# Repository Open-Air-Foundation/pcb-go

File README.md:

# AirGradient GO — Hardware

> KiCad hardware design files for the AirGradient GO, a portable battery-powered air quality monitor.

<!--  -->

**This checkout is v2:** main board PCB revision 2.1, the boards in the GO v2 production units (tag `v2`, branch `main`).

## Overview

AirGradient GO is a handheld air quality monitor. It measures:
- particulate matter (Sensirion SPS30);
- CO₂ (Senseair S12);
- VOC/NOx (Sensirion SGP41);
- temperature and humidity (Sensirion SHT40);
- barometric pressure (Goermicro SPL07-003).

It also has an accelerometer (LIS2DH12) for motion detection and a GNSS receiver (TAU1113, GPS L1 and BeiDou B1) for location.

Readings are shown on a 2.13″ black-and-white e-paper display, with four RGB LEDs and capacitive touch controls. The device runs on a replaceable 18500 Li-ion cell (2600 mAh), charged over USB-C.

This repository contains the complete electronics design: schematics, PCB layouts, shared component libraries, and production outputs.

## Versions

| Version | Where | Main board revision | State |
|---|---|---|---|
| v1 | tag `v1.0` | 1.0 | the first product: pouch cell, separate LED + touch board |
| v2 | tag `v2`, branch `main` | 2.1 | **the produced boards** (this checkout) |
| v3 | branch `v3-reroute` | 3.0 | prototype |

[VERSIONS.md](https://github.com/Open-Air-Foundation/pcb-go/blob/v3-reroute/VERSIONS.md) (on branch `v3-reroute`) compares the three side by side, with pin maps and the reasons for each change.

Each version has a hardware spec sheet. It includes the parts the KiCad BOM does not define: the display, the battery and the internal cables.
- v2: [SPEC-SHEET.md](SPEC-SHEET.md)
- v1: [SPEC-SHEET-v1.md](SPEC-SHEET-v1.md)
- v3: [SPEC-SHEET.md on branch `v3-reroute`](https://github.com/Open-Air-Foundation/pcb-go/blob/v3-reroute/SPEC-SHEET.md)

The manufacturers' documents (PDF) are in [`documents/`](documents/README.md): datasheets of the main parts (ESP32-C5 module, charger, fuel gauge, power parts, sensors, peripherals), and the documents a search does not find (display, battery, Senseair S12, GNSS antenna).

[`CLAUDE.md`](CLAUDE.md) and [`AGENTS.md`](AGENTS.md) are instructions for an AI working in this repository: which git ref is which version, which document answers which question, the traps.

## Boards in this repository

| Board | Directory | Production set | Layers | Used by | Description |
|---|---|---|---|---|---|
| Main board | `PCB/airgradient-go-main/` | `Airgradient-GO_2.1` | 4 | v2 | MCU, power and charging, cell protection and fuel gauge, sensors, LEDs, storage. `Airgradient-GO_2.0` is the prototype revision |
| Touch pad | `PCB/touch-pad/` | `Touch_sensor_v2.1` | 2 | v2 | Three capacitive pads with the CAP1203 controller; 5-pin cable to the main board |
| LED + touch controller | `PCB/led-touch/` | `AG-GO-LED_1.0` | 2 | v1 only | RGB LEDs, LED driver and touch controller of v1 |
| SCD4x module | `PCB/scd4x-module/` | `SCD4x_module_0.1` | 2 | optional | CO₂ daughterboard. The standard configuration uses the on-board Senseair S12 |

## Key components (main board 2.1)

| Function | Part | Ref |
|---|---|---|
| MCU / Wi-Fi 6 + Bluetooth LE | ESP32-C5-MINI-1 (N4) | U4 |
| Battery charger | BQ25628 | U5 |
| Fuel gauge and cell protection | BQ27742-G1, with the CSD83325L FET pair | U3, Q3 |
| Input power switch | LM66200 ideal-diode switch | U19 |
| Buck-boost converter (3.1 V rail) | TPS63802 | U8 |
| LDO, GNSS backup supply | TPS7A0228 | U9 |
| Hardware watchdog | TPL5010 | U7 |
| NAND flash (512 Mb) | W25N512GVEIG | U1 |
| NAND flash, alternative footprint (not fitted) | ZDSD512MLGEAG | U2 |
| microSD socket (not fitted) | TF-CARD XG8P | TF1 |
| CO₂ sensor module | Senseair S12 | U16 |
| VOC/NOx sensor | SGP41 | U10 |
| Temperature/humidity sensor | SHT40 | U12 |
| Pressure sensor | SPL07-003 | U13 |
| Accelerometer | LIS2DH12 | U14 |
| GNSS receiver | TAU1113 | U18 |
| GNSS antenna | CA-G01 chip antenna | AE1 |
| I²C switch for the SPS30 | TMUX121 | U15 |
| I/O expander | TCA6408A | U17 |
| LED driver, 4 RGB LEDs | LP5036 | U20, LED1–LED4 |
| Buzzer | HYG-8503A | U6 |
| USB-C connector | GT-USB-7010ASV | USB1 |
| CO sensor place (not fitted) | — | U11 |

The cable connectors are HCZZ0032-5 (5-pin, 1.0 mm), referenced `CN1` to `CN3`:
- `CN1` takes the Sensirion SPS30 PM module.
- `CN2` takes the touch pad.
- `CN3` is a spare I²C header.

The cell sits in a moulded holder whose contacts are on the board (`BT1`), in a cut-out at the top of the board.

## Toolchain

- **KiCad 10** (file format 2026-03). All symbol, footprint, and 3D model libraries are bundled in `libraries/`. Each board's `fp-lib-table` / `sym-lib-table` references them project-relative, so the projects open without any extra library setup.
- **[Fabrication Toolkit](https://github.com/bennymeg/Fabrication-Toolkit)** plugin generates the Gerber/BOM/CPL production sets (`fabrication-toolkit-options.json` per board).

## Repository structure

```
PCB/
├── airgradient-go-main/     # Main PCB (schematic, layout, BOM.csv, production/)
├── touch-pad/               # Capacitive touch PCB
├── led-touch/               # LED + touch-controller PCB (v1 only)
└── scd4x-module/            # Optional SCD4x CO₂ daughterboard
libraries/                   # Shared KiCad symbols, footprints, 3D models
graphics/                    # Logos and artwork
SPEC-SHEET.md                # Hardware spec sheet of v2
SPEC-SHEET-v1.md             # Hardware spec sheet of v1
documents/                   # Manufacturers' documents: datasheets of the main parts, display, battery, S12
CLAUDE.md                    # Instructions for AI agents
AGENTS.md                    # Points other AI agents to CLAUDE.md
```

## Fabrication

Each board's `production/` directory holds a ready-to-order set: Gerber zip, BOM, designators, and pick-and-place positions in JLCPCB-compatible format (generated with Fabrication Toolkit). For v2 the sets are `Airgradient-GO_2.1` (main board) and `Touch_sensor_v2.1` (touch pad).

The main board is 4 layers, 0.8 mm thick. The touch, LED and SCD4x boards are 2 layers.

## BOM & sourcing

The schematic BOM is `PCB/airgradient-go-main/BOM.csv`. The assembly BOMs (`production/*_bom.csv`) carry LCSC part numbers for assembly at JLCPCB.

These main-board parts have no LCSC number and are supplied separately for assembly:
- ESP32-C5-MINI-1 module
- Senseair S12
- SGP41
- SHT40
- TAU1113
- CA-G01 antenna

The display, the battery and the two internal cables are not in the KiCad BOM: see [SPEC-SHEET.md](SPEC-SHEET.md). The datasheets of the main parts, and the manufacturers' documents for the display, the battery, the S12 and the GNSS antenna, are in [`documents/`](documents/README.md).

## Versioning & releases

Hardware versions are tagged on this repository: `v1.0`, `v2`. Per-version release notes, with chip-level changes, design history and the matching production file set, are published on the [GitHub Releases](../../releases) page.

## Related repositories

<!-- TODO: add links to the firmware and enclosure repositories -->

## License

This is open-source hardware. The design files in this repository are licensed under the
[Creative Commons Attribution-ShareAlike 4.0 International (CC BY-SA 4.0)](https://creativecommons.org/licenses/by-sa/4.0/) license — see [LICENSE](LICENSE).

You are free to use, modify, and manufacture these designs, including commercially, provided you credit AirGradient and share derivative designs under the same license.

## Maintainers

AirGradient hardware team.

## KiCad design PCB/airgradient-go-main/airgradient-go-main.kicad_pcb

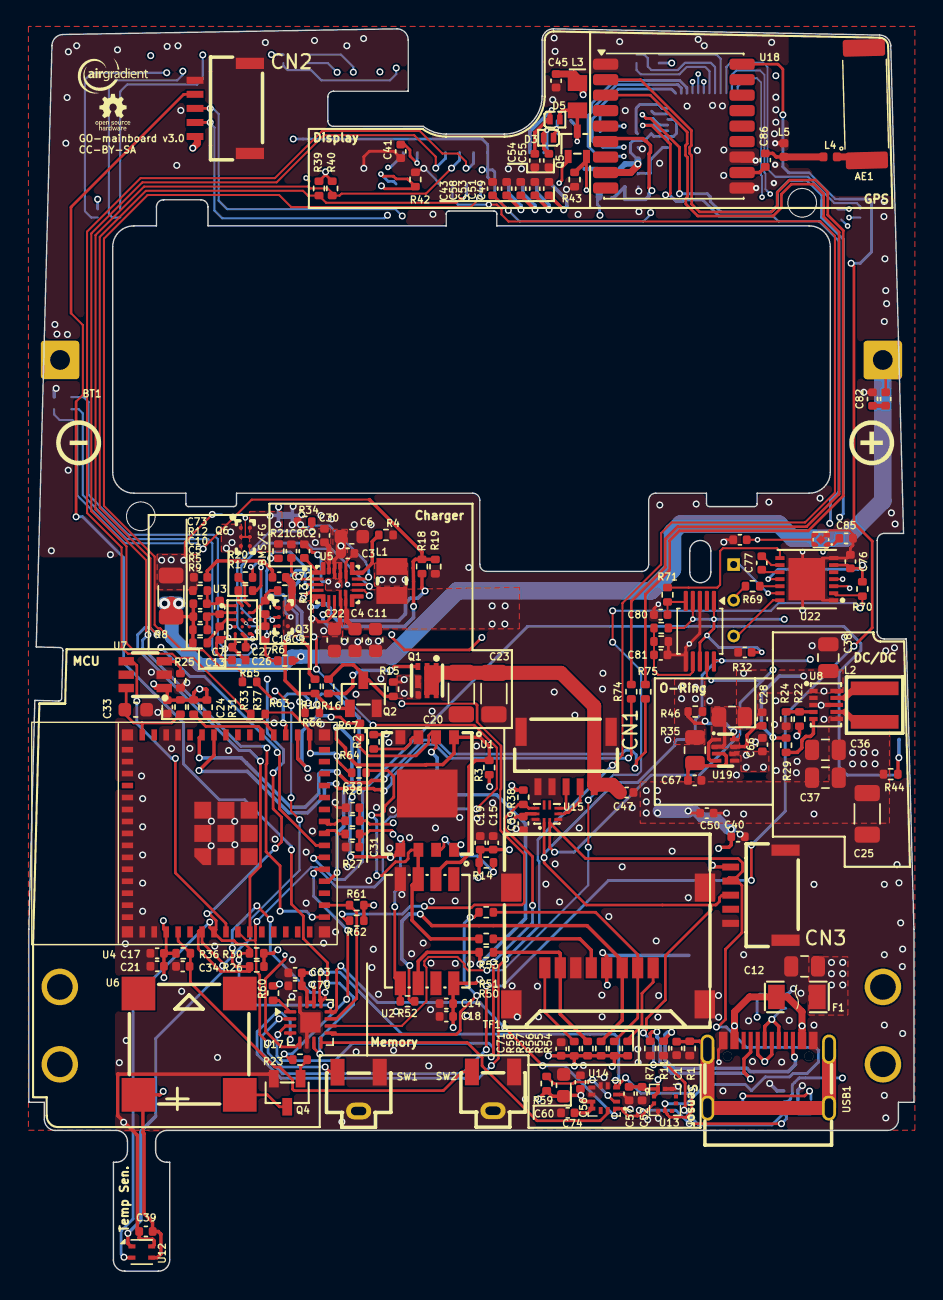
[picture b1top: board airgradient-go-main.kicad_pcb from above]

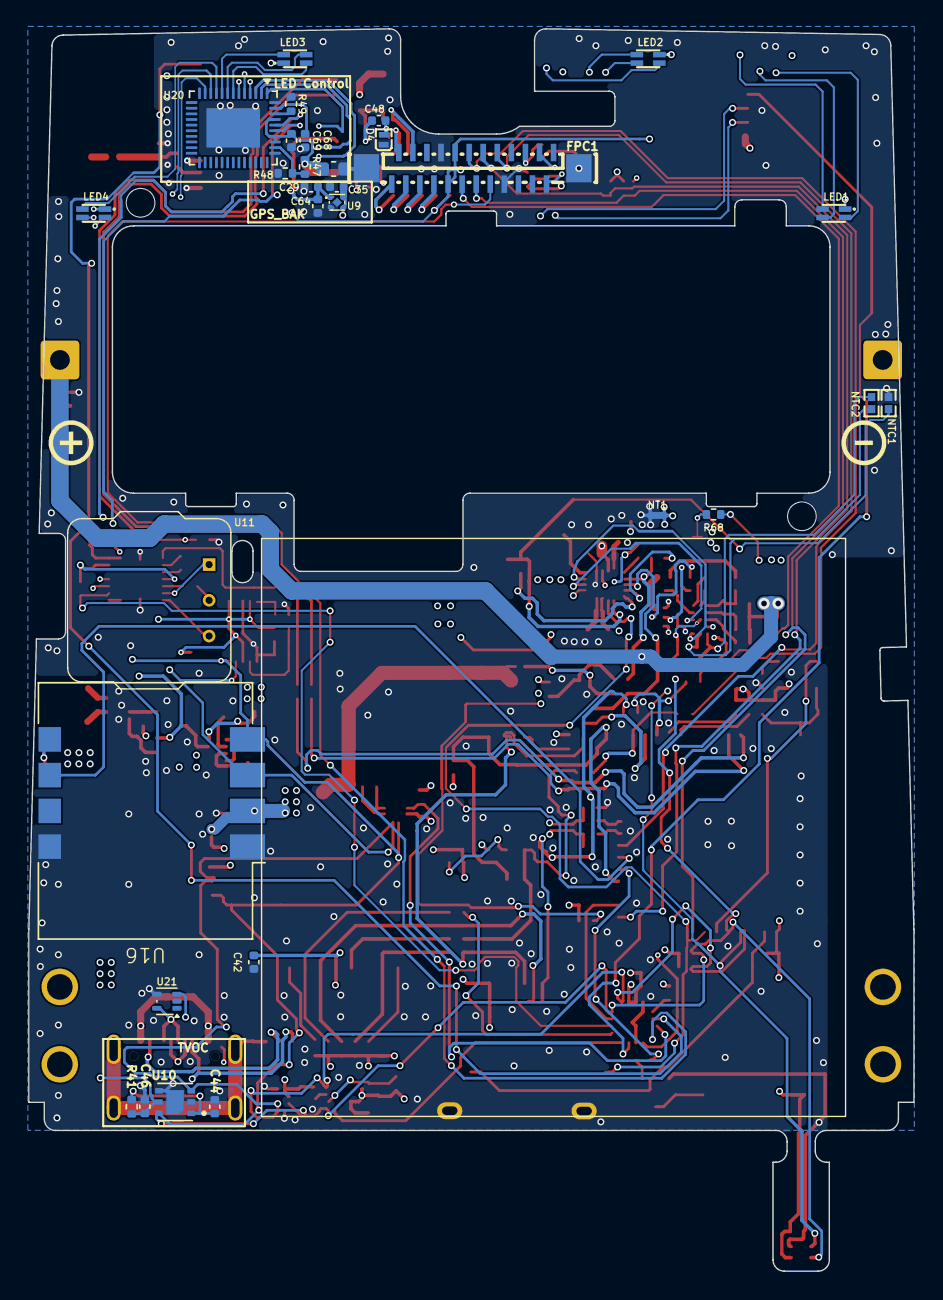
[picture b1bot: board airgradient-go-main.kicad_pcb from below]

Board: 4 copper layers, 62.9 x 88.3 mm, 212 parts (30 on the bottom side), 143 nets.

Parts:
AE1: CA-G01
BT1: Battery_Cell; AGGO-battery
C1, C3, C5, C7, C9, C10, C13, C14, C15, C16, C24, C28, C39, C52, C56, C57, C59, C63, C70, C71, C72, C73, C74, C75, C77, C79, C82: 0.1uF/25V; C_0402_1005Metric
C2, C81: 47nF/25V; C_0402_1005Metric
C4, C6, C11, C22, C60, C65: 10uF/25V; C_0603_1608Metric
C8, C45, C48: 4.7uF/25V; C_0402_1005Metric
C12, C36, C37, C38: 22uF/25V; C_0805_2012Metric
C17: 0.1uF/10V; C_0402_1005Metric
C18, C19, C26, C29, C30, C35, C40, C41, C42, C43, C44, C46, C47, C49, C50, C51, C53, C54, C55, C58, C64, C66, C67, C68, C80: 1uF/50V; C_0402_1005Metric
C20: 47uF/25V; C_1206_3216Metric
C21: 22uF/10V; C_0402_1005Metric
C23, C25: DNP; C_1206_3216Metric
C27: 0.47uF/25V; C_0402_1005Metric
C31, C32: 1nF/50V; C_0402_1005Metric
C33: 500pF/50V; C_0603_1608Metric
C34: 10nF/10V; C_0402_1005Metric
C69: 0.1uF/16V; C_0402_1005Metric
C76, C84, C85: 1uF/25V; C_0402_1005Metric
C86: 100pF/50V; C_0402_1005Metric
CN1, CN2, CN3: HCZZ0032-5; CONN-SMD_HCZZ0032-5
D3, D4, D5: PMEG3005EL,315; SOD-882_L1.0-W0.6-RD
F1: BSMD1206-260-6V; F1206
FPC1: FPC 0.5-24P LTH2.0; FPC-SMD_FPC-0.5-24P-LTH2.0
L1: 252012CDMCDDS-1R0MC; IND-SMD_L2.5-W2.0
L2: XGL4020-471MEC; IND-SMD_L4.0-W4.0_XGL4020
L3: XRIM201210S100MBCA; L0805
L4, L5: 6.2nH; L_0402_1005Metric
LED1, LED2, LED3, LED4: TJ-S1608SW6TDSLCCYRGB-A5; LED-ARRAY-SMD_4P-L1.6-W0.8-BL-FD
NT1: NetTie_2; NetTie-2_SMD_Pad0.5mm
NTC1, NTC2: NCP15XH103F03RC; R0402
Q1: SIA445EDJ-T1-GE3; SC-70-6L_L2.0-W2.0-P0.65-BL
Q2: ZVN4106FTA_C508255; SOT-23-3_L2.9-W1.3-P1.90-LS2.4-BR
Q3, Q6: CSD83325L; PICOSTAR-6_L2.2-W1.1-R2-C3-P0.65-BL
Q4: SS8050-G; SOT-23-3_L2.9-W1.3-P1.90-LS2.4-BR
Q5: SI1308EDL; SOT-323-3_L2.0-W1.3-P1.30-LS2.1-BR
R1, R2, R3, R4, R14, R26, R29, R30, R31, R33, R38, R39, R40, R44, R46, R59, R60, R61, R62, R70: 100K; R_0402_1005Metric
R5, R12: 200R; R_0402_1005Metric
R6, R9: 10R; R_0402_1005Metric
R7, R11: 5.1K; R_0402_1005Metric
R8: 5mR 1%/1W; R_1206_3216Metric
R10, R34, R36, R37, R49, R54, R55, R56, R57, R58, R68: 10K; R_0402_1005Metric
R13: 2K; R_0402_1005Metric
R15: 15K; R_0402_1005Metric
R16: 20K; R_0402_1005Metric
R17, R20, R23, R71: 1K; R_0402_1005Metric
R18: 5.23k; R_0402_1005Metric
R19: 30.1k; R_0402_1005Metric
R21: 1.1K; R_0402_1005Metric
R22: 511K; R_0402_1005Metric
R24: 91K; R_0402_1005Metric
R25: 51K; R_0402_1005Metric
R27, R28, R50, R51, R52, R53: 22R; R_0402_1005Metric
R32: 50mR; R_0805_2012Metric
R35: 470mR; R_0805_2012Metric
R41: 4.7R; R_0402_1005Metric
R42: 1M; R_0402_1005Metric
R43: 2.2R; R_0402_1005Metric
R47, R48: 0R; R_0402_1005Metric
R63, R64, R65, R66, R67: 33R; R_0402_1005Metric
R69: 100R; R_0402_1005Metric
R72: 120K; R_0402_1005Metric
R73: 30K; R_0402_1005Metric
R74, R75: 499R; R_0402_1005Metric
SW1, SW2: TS-1091C-A1B3-D2; KEY-SMD_3P-L5.5-W3.8-P3.00
TF1: TF-CARD XG8P H1.5; TF-SMD_TF-CARD-XG8P-H1.5
U1: W25N512GVEIG; WSON-8_L8.0-W6.0-P1.27-TL-1
U2: ZDSD512MLGEAG; LGA-8_L8.0-W6.0-P1.27-TL
U3: BQ27742YZFR-G1; DSBGA-15_L2.6-W2.0-R5-C3-P0.50-BL
U4: ESP32-C5-MINI-1
U5: BQ25628RYKR; WQFN-18_L3.0-W2.5-P0.40-TL
U6: HYG-8503A; BUZ-SMD_4P-L8.5-W8.5-P8.50-BR
U7: TPL5010DDCR; SOT-23-6_L2.9-W1.6-P0.95-LS2.8-BR
U8: TPS63802DLAR; VSON-10_L3.0-W2.0-P0.50-TL
U9: TPS7A0228DQNR; X2SON-4_L1.0-W1.0-P0.65-TL-EP
U10: SGP41-D-R4; XDCR_SGP41-D-R4
U11: ES1-CO-100-01; PS1-CO-SMOKE-10k
U12: SHT4x; Sensirion_DFN-4_1.5x1.5mm_P0.8mm_SHT4x_NoCentralPad
U13: SPL07-003; LGA-10_L2.0-W2.0-P0.50-BL
U14: LIS2DH12TR; LGA-12_L2.0-W2.0-P0.50-BL
U15: TMUX121NKGR_C22428404; UQFN-10_L1.8-W1.4-P0.40-BL
U16: S12; S12_rev2
U17: TCA6408ARGT; VQFN-16-1EP_3x3mm_P0.5mm_EP1.45x1.45mm
U18: TAU1113
U19: LM66200DRLR; SOT-583-8_L2.1-W1.2-P0.50-LS1.6-BL
U20: LP5036; VQFN-46-1EP_5x6mm_P0.4mm_EP2.8x3.8mm
U21: TPD2E2U06DRLR; SOT-553
U22: LMP91002SDX/NOPB; WSON-14_L4.0-W4.0-P0.50-BL-EP
U23: ADS1115IDGSR; TSSOP-10_3x3mm_P0.5mm
U24: TPS7A2030PDQNR; X2SON-4_L1.0-W1.0-P0.65-TL-EP
USB1: GT-USB-7010ASV; USB-C-SMD_G-SWITCH_GT-USB-7010ASV

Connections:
+3.3V: C14.2, C15.2, C17.2, C18.2, C19.2, C21.2, C24.2, C25.1, C36.2, C37.2, C39.2, C40.2, C42.2, C43.2, C45.2, C46.2, C50.2, C52.2, C56.2, C57.2, C59.2, C60.2, C63.2, C65.2, C69.2, C70.2, C71.2, C74.2, CN2.1, CN3.5, FPC1.15, FPC1.16, L3.1, LED1.1 (+), LED2.1 (+), LED3.1 (+), LED4.1 (+), R2.2, R3.2, R14.2, R22.2, R26.2, R30.2, R31.2, R33.2, R36.2, R37.2, R38.2, R39.1, R40.1, R41.2, R44.2, R47.1, R54.2, R55.2, R56.2, R57.2, R58.2, R59.2, R60.2, R61.2, R62.2, TF1.4 (VDD), U1.8 (VCC), U2.8 (VDD), U4.3 (3V3), U6.1 (+), U7.1 (VDD), U8.6 (VOUT), U10.5 (VDDH), U12.3 (VDD), U13.1 (VDDIO), U13.10 (VDD), U14.9 (VDD), U14.10 (VDD_IO), U15.9 (VDD), U16.2 (VCC), U17.14 (V_{CCP}), U17.15 (V_{CCI}), U18.8 (VCC), U20.39 (ADDR1), U20.40 (VCC), U20.43 (EN)
+5V: C20.2, C23.1, C47.2, CN1.1, Q1.1 (D), Q1.2 (D), Q1.5 (D), Q1.6 (D), Q1.8 (D)
/ACC_INT: U14.12 (INT1), U17.8 (P5)
/BAT+: BT1.1 (+), C5.1, C10.2, C75.1, R5.1, R6.1, R8.1, R9.1
/BAT+_RS: C73.2, Q3.A1 (S), Q3.C1 (S), R8.2, R12.1, R68.2
/BAT-: C9.2, C13.2, C16.2, C26.1, NT1.1, Q6.A2, Q6.C2, U3.D1 (VSS)
/BTST: C2.1, U5.1 (BTST)
/BUZZ: R23.1, U4.20 (IO8)
/CE: R4.2, U5.14 (~CE)
/CELL-: BT1.2 (-), Q6.A1, Q6.C1
/CHG_INT: R62.1, U5.11 (~INT), U17.5 (P3)
/CO_AIN1: C80.1, R71.2, U23.5
/CO_CE: U11.3 (C), U22.14
/CO_MENB: R70.1, U17.10 (P7), U22.2
/CO_RE: U11.1 (R), U22.13
/CO_S: R69.2, U11.2 (S)
/CO_VOUT: R71.1, U22.8
/CO_ZERO: C81.1, R72.2, R73.1, U23.7
/EEPA: U4.21 (IO9), U16.6 (EEPA)
/EN: C33.2, R31.1, U4.45 (EN), U7.6 (RSTn)
/EN_PM1: R38.1, U15.8 (~EN), U17.3 (P1)
/EXP_INT: R61.1, U4.17 (IO1), U17.11 (~INT)
/GDR: FPC1.2, Q5.1 (G), R42.2
/GNSS_RF: C86.2, U18.11 (RF_IN)
/GNSS_T: C86.1, L4.2, L5.1
/INT: CN2.4, U17.7 (P4)
/IO26: R37.1, U4.34 (IO26)
/IO27: R33.1, U4.35 (IO27)
/IO28: C34.2, R36.1, SW2.1, U4.4 (IO28)
/LED_1_B: LED1.2 (-), U20.1 (OUT0)
/LED_1_G: LED1.3 (-), U20.2 (OUT1)
/LED_1_R: LED1.4 (-), U20.3 (OUT2)
/LED_2_B: LED2.2 (-), U20.4 (OUT3)
/LED_2_G: LED2.3 (-), U20.5 (OUT4)
/LED_2_R: LED2.4 (-), U20.6 (OUT5)
/LED_3_B: LED3.2 (-), U20.7 (OUT6)
/LED_3_G: LED3.3 (-), U20.8 (OUT7)
/LED_3_R: LED3.4 (-), U20.9 (OUT8)
/LED_4_B: LED4.2 (-), U20.10 (OUT9)
/LED_4_G: LED4.3 (-), U20.11 (OUT10)
/LED_4_R: LED4.4 (-), U20.12 (OUT11)
/MCU_RX: R75.1, U18.2 (TXD1)
/MCU_TX: R74.2, U18.3 (RXD1)
/MISO: R67.1, U4.32 (IO24)
/MOSI: R65.1, R66.1, U4.33 (IO25)
/NAND CS: R3.1, U1.1 (/CS), U2.2 (DATA3), U4.19 (IO7)
/NAND MISO: R50.1, R67.2, U1.2 (DO(IO1)), U2.6 (DATA0)
/NAND MOSI: R52.2, R66.2, U1.5 (DI(IO0)), U2.5 (CMD)
/NAND SCLK: R51.1, R64.2, U1.6 (CLK), U2.3 (CLK)
/PMID_GD: Q2.1 (G), R10.2, U5.3 (PMID_GD)
/PM_SCL: CN1.3, U15.5 (S1A)
/PM_SDA: CN1.2, U15.4 (S2A)
/PREVGH: C54.2, D5.1, FPC1.21
/PREVGL: C55.2, D3.2, FPC1.23
/PRTRG: U17.2 (P0), U18.18 (PRTRG)
/QON: SW1.1, U4.9 (IO5), U5.7 (~QON)
/REGN: C8.2, R10.1, U5.2 (REGN)
/RESE: FPC1.3, Q5.2 (S), R43.2
/SCL: CN2.3, CN3.3, R30.1, U3.E3 (SCL), U4.7 (IO3), U5.13 (SCL), U10.6 (SCL), U12.2 (SCL), U13.2 (SCL), U14.1 (SCL/SPC), U15.1 (D1), U16.4 (Tx/SCL), U17.12 (SCL), U20.42 (SCL), U22.3, U23.10
/SCLK: R63.1, R64.1, U4.31 (IO23)
/SDA: CN2.2, CN3.4, R26.1, U3.C3 (SDA), U4.6 (IO2), U5.12 (SDA), U10.3 (SDA), U12.1 (SDA), U13.4 (SDA), U14.4 (SDA/SDI/SDO), U15.2 (D2), U16.3 (Rx/SDA), U17.13 (SDA), U20.41 (SDA), U22.4, U23.9
/SD_CS: R53.2, U17.9 (P6)
/SW: C2.2, L1.1, U5.16 (SW)
/U0RXD: R75.2, U4.40 (RXD0)
/U0TXD: R74.1, U4.39 (TXD0)
/USB+: R28.1, U4.24 (IO14)
/USB-: R27.2, U4.23 (IO13)
/USB_D+: C32.2, R28.2, U21.5, USB1.A6 (DP1), USB1.B6 (DP2)
/USB_D-: C31.2, R27.1, U21.3, USB1.A7 (DN1), USB1.B7 (DN2)
/VCOM: C49.2, FPC1.24
/WD_RST: U4.8 (IO4), U7.4 (DONE)
/ePaper BUSY: FPC1.9, U4.22 (IO10)
/ePaper CS: FPC1.12, R39.2, U4.10 (IO6)
/ePaper D/C: FPC1.11, R40.2, U4.16 (IO0)
/ePaper MOSI: FPC1.14, R65.2
/ePaper RES: FPC1.10, U17.4 (P2)
/ePaper SCLK: FPC1.13, R63.2
GND: C1.1, C3.1, C4.1, C6.1, C8.1, C11.1, C12.1, C14.1, C15.1, C17.1, C18.1, C19.1, C20.1, C21.1, C22.1, C23.2, C24.1, C25.2, C28.1, C29.1, C30.1, C31.1, C32.1, C33.1, C34.1, C35.1, C36.1, C37.1, C38.1, C39.1, C40.1, C41.1, C42.1, C43.1, C44.1, C45.1, C46.1, C47.1, C49.1, C50.1, C51.1, C52.1, C53.1, C54.1, C55.1, C56.1, C57.1, C58.1, C59.1, C60.1, C63.1, C64.1, C65.1, C66.1, C67.1, C68.1, C69.1, C70.1, C71.1, C74.1, C76.2, C79.2, C80.2, C81.2, C82.2, C84.2, C85.2, CN1.4, CN1.5, CN1.6, CN1.7, CN2.5, CN2.6, CN2.7, CN3.1, CN3.6, CN3.7, D4.1, FPC1.8, FPC1.17, FPC1.25, FPC1.26, L5.2, NT1.2, NTC1.2, Q2.2 (S), Q4.2 (E), R1.1, R4.1, R7.1, R11.1, R19.1, R21.1, R24.2, R25.1, R34.1, R42.1, R43.1, R48.1, R49.1, R73.2, SW1.2, SW1.3, SW2.2, SW2.3, TF1.6 (VSS), TF1.9 (GND), TF1.10 (GND), TF1.11 (GND), TF1.12 (GND), U1.4 (GND), U1.9 (GND), U2.4 (GND), U4.1 (GND), U4.2 (GND), U4.42 (GND), U4.43 (GND), U4.46 (GND), U4.47 (GND), U4.48 (GND), U4.50 (GND), U4.51 (GND), U4.52 (GND), U4.53 (GND), U4.54 (GND), U4.55 (GND), U4.56 (GND), U4.57 (GND), U4.58 (GND), U4.59 (GND), U4.60 (GND), U4.61 (GND), U4.62 (GND), U4.63 (GND), U4.64 (GND), U4.65 (GND), U5.15 (GND), U7.2 (GND), U8.2 (MODE), U8.3 (AGND), U8.8 (GND), U9.2 (GND), U9.5 (EP), U10.2 (VSS), U10.4 (N/A), U10.7 (EXP), U12.4 (VSS), U13.3 (GND), U13.8 (GND), U13.9 (GND), U14.3 (SDO/SA0), U14.5 (RES), U14.6 (GND), U14.7 (GND), U14.8 (GND), U15.3 (GND), U15.10 (SEL), U16.1 (GND), U16.8 (COMSEL), U17.6 (GND), U17.16 (ADDR), U17.17 (EPAD), U18.1 (GND), U18.10 (GND), U18.12 (GND), U19.1 (GND), U19.4 (~ON), U19.5 (GND), U20.37 (GND), U20.46 (GND), U20.47 (GND), U21.4, U22.1, U22.7, U22.15, U23.3, U23.6, U24.2, U24.5, USB1.A1B12 (GND), USB1.B1A12 (GND)
unnamed: AE1.1, L4.1
unnamed: C1.2, R1.2, USB1.1 (SHELL), USB1.2 (SHELL), USB1.3 (SHELL), USB1.4 (SHELL)
unnamed: C28.2, R32.1, U19.2 (VOUT), U19.7 (VOUT)
unnamed: C41.2, FPC1.5
unnamed: C48.2, D3.1, D4.2
unnamed: C51.2, FPC1.22
unnamed: C53.2, FPC1.20
unnamed: C58.2, FPC1.18
unnamed: C72.2, C73.1
unnamed: C75.2, C82.1
unnamed: F1.1, USB1.A4B9 (VBUS), USB1.B4A9 (VBUS)
unnamed: Q1.3 (G), R16.2
unnamed: Q2.3 (D), R15.2, R16.1
unnamed: Q3.B1 (G), R17.2
unnamed: Q3.B2 (G), R20.2
unnamed: Q4.1 (B), R23.2
unnamed: Q4.3 (C), U6.2 (-)
unnamed: C48.1, D5.2, L3.2, Q5.3 (D)
unnamed: Q6.B1, Q6.B2, R68.1
unnamed: R53.1, R55.1, TF1.2 (CD/DAT3)
unnamed: R51.2, TF1.5 (CLK)
unnamed: R52.1, R56.1, TF1.3 (CMD)
unnamed: R50.2, R57.1, TF1.7 (DAT0)
unnamed: R58.1, TF1.8 (DAT1)
unnamed: R54.1, TF1.1 (DAT2)
unnamed: R14.1, U1.7 (/HOLD(IO3))
unnamed: R2.1, U1.3 (/WP(IO2))
unnamed: C9.1, R6.2, U3.C2 (BAT)
unnamed: R17.1, U3.A2 (CHG)
unnamed: R20.1, U3.A3 (DSG)
unnamed: C16.1, R13.2, U3.B3 (PACKP)
unnamed: C26.2, C27.1, NTC2.1, U3.E1 (REG25)
unnamed: C5.2, C7.2, R5.2, U3.B1 (SRN)
unnamed: C7.1, C10.1, R12.2, U3.A1 (SRP)
unnamed: C27.2, NTC2.2, U3.E2 (TS)
unnamed: C13.1, R9.2, U3.C1 (VPWR)
unnamed: R21.2, U5.4 (ILIM)
unnamed: NTC1.1, R18.1, R19.2, U5.6 (TS)
unnamed: R18.2, U5.5 (TS_BIAS)
unnamed: R25.2, U7.3 (DELAY/M_RST)
unnamed: C38.2, R29.1, R32.2, U8.1 (EN), U8.10 (VIN)
unnamed: R22.1, R24.1, U8.4 (FB)
unnamed: L2.1, U8.9 (L1)
unnamed: L2.2, U8.7 (L2)
unnamed: R29.2, U8.5 (PG)
unnamed: C44.2, R41.1, U10.1 (VDD)
unnamed: R59.1, U14.2 (CS)
unnamed: R44.1, U16.5 (EN)
unnamed: R60.1, U17.1 (~RESET)
unnamed: R46.2, U19.8 (ST)
unnamed: C67.2, R35.2, U19.3 (VIN1)
unnamed: R47.2, R48.2, U20.38 (ADDR0)
unnamed: R49.2, U20.44 (IREF)
unnamed: C68.2, U20.45 (VCAP)
unnamed: C77.1, U22.10
unnamed: C77.2, U22.9
unnamed: R69.1, U22.12
unnamed: R7.2, USB1.A5 (CC1)
unnamed: R11.2, USB1.B5 (CC2)
PMID: C3.2, C6.2, Q1.4 (S), Q1.7 (S), R15.1, U5.17 (PMD)
Pack+: C22.2, C35.2, C72.1, C84.1, Q3.A2 (S), Q3.C2 (S), R13.1, U5.8 (BAT), U9.3 (EN), U9.4 (IN), U24.3, U24.4
SYS: C4.2, C11.2, C66.2, L1.2, U5.9 (SYS), U19.6 (VIN2)
VBUS: C12.2, C30.2, F1.2, R34.2, R35.1, R46.1, U5.18 (VBUS)
VDD_BAK: C29.2, C64.2, U9.1 (OUT), U18.6 (V_BCKP)
VDD_CO: C76.1, C79.1, C85.1, R70.2, R72.1, U22.6, U22.11, U23.1, U23.4, U23.8, U24.1

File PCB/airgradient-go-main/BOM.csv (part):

"Reference","Qty","Value","DNP","Exclude from BOM","Exclude from Board","Footprint","Datasheet","LCSC Part"
"USB1","1","GT-USB-7010ASV","","","","easyeda2kicad-oaf:USB-C-SMD_G-SWITCH_GT-USB-7010ASV","","C2988369"
"U20","1","LP5036","","","","Package_DFN_QFN:VQFN-46-1EP_5x6mm_P0.4mm_EP2.8x3.8mm","https://www.lcsc.com/product-detail/C701961.html","C701961"
"U19","1","LM66200DRLR","","","","easyeda2kicad-oaf:SOT-583-8_L2.1-W1.2-P0.50-LS1.6-BL","","C3235556"
"U17","1","TCA6408ARGT","","","","Package_DFN_QFN:VQFN-16-1EP_3x3mm_P0.5mm_EP1.45x1.45mm","https://www.lcsc.com/product-detail/C181499.html","C181499"
"U16","1","S12","","","","S12-oaf:S12","",""
"U15","1","TMUX121NKGR_C22428404","","","","easyeda2kicad-oaf:UQFN-10_L1.8-W1.4-P0.40-BL","","C22428404"
"U14","1","LIS2DH12TR","","","","easyeda2kicad-oaf:LGA-12_L2.0-W2.0-P0.50-BL","https://lcsc.com/product-detail/Motion-Sensors-Accelerometer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","C110926"
"U13","1","SPL07-003","","","","easyeda2kicad-oaf:LGA-10_L2.0-W2.0-P0.50-BL","","C3253727"
"U9","1","TPS7A0228DQNR","","","","easyeda2kicad-oaf:X2SON-4_L1.0-W1.0-P0.65-TL-EP","","C5220175"
"U8","1","TPS63802DLAR","","","","easyeda2kicad-oaf:VSON-10_L3.0-W2.0-P0.50-TL","","C2845237"
"U7","1","TPL5010DDCR","","","","easyeda2kicad-oaf:SOT-23-6_L2.9-W1.6-P0.95-LS2.8-BR","https://lcsc.com/product-detail/Timer_Texas-Instruments-Texa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","C473912"
"U6","1","HYG-8503A","","","","easyeda2kicad-oaf:BUZ-SMD_4P-L8.5-W8.5-P8.50-BR","","C7544813"
"U5","1","BQ25628RYKR","","","","easyeda2kicad-oaf:WQFN-18_L3.0-W2.5-P0.40-TL","","C6055599"
"U4","1","ESP32-C5-MINI-1","","","","Esparessif-oaf:ESP32-C5-MINI-1","https://documentation.espressif.com/esp32-c5-mini-1_datashee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",""
"U3","1","BQ27742YZFR-G1","","","","easyeda2kicad-oaf:DSBGA-15_L2.6-W2.0-R5-C3-P0.50-BL","","C2842397"
"U1","1","W25N512GVEIG","","","","easyeda2kicad-oaf:WSON-8_L8.0-W6.0-P1.27-TL-1","","C3024446"
"TF1","1","TF-CARD XG8P H1.5","DNP","","","easyeda2kicad-oaf:TF-SMD_TF-CARD-XG8P-H1.5","","C7529392"
"SW1,SW2","2","TS-1091C-A1B3-D2","","","","easyeda2kicad-oaf:KEY-SMD_3P-L5.5-W3.8-P3.00","","C2874581"
"R54,R55,R56,R57,R58","5","10K","DNP","","","Resistor_SMD:R_0402_1005Metric","https://lcsc.com/product-detail/Others_Huaxin-S-T-MR04X1002F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","C327797"
"R50,R51,R52,R53","4","22R","DNP","","","Resistor_SMD:R_0402_1005Metric","https://lcsc.com/product-detail/Chip-Resistor-Surface-Mount_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","C114765"
"R45,R47","2","0R","","","","Resistor_SMD:R_0402_1005Metric","https://lcsc.com/product-detail/Chip-Resistor-Surface-Mount_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","C106231"
"R43","1","2.2R","","","","Resistor_SMD:R_0402_1005Metric","https://lcsc.com/product-detail/Chip-Resistor-Surface-Mount-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","C25101"
"R42","1","1M","","","","Resistor_SMD:R_0402_1005Metric","https://lcsc.com/product-detail/Chip-Resistor-Surface-Mount_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","C138033"
"R41","1","4.7R","","","","Resistor_SMD:R_0402_1005Metric","","C2909356"
"R35","1","470mR","","","","Resistor_SMD:R_0805_2012Metric","https://www.lcsc.com/product-detail/C705493.html","C705493"
"R32","1","50mR","","","","Resistor_SMD:R_0805_2012Metric","https://www.lcsc.com/product-detail/C247602.html","C247602"
"R27,R28","2","22R","","","","Resistor_SMD:R_0402_1005Metric","https://lcsc.com/product-detail/Chip-Resistor-Surface-Mount_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","C114765"
"R25","1","51K","","","","Resistor_SMD:R_0402_1005Metric","https://lcsc.com/product-detail/Chip-Resistor-Surface-Mount_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","C107229"
"R24","1","91K","","","","Resistor_SMD:R_0402_1005Metric","https://lcsc.com/product-detail/Others_YAGEO-RC0402FR-0791KL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","C327323"
"R22","1","475K","","","","Resistor_SMD:R_0402_1005Metric","","C5713272"
"R21","1","2.49K","","","","Resistor_SMD:R_0402_1005Metric","https://lcsc.com/product-detail/Chip-Resistor-Surface-Mount-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","C25884"
"R19","1","30.1k","","","","Resistor_SMD:R_0402_1005Metric","https://www.lcsc.com/product-detail/C29402.html","C29402"
"R18","1","5.23k","","","","Resistor_SMD:R_0402_1005Metric","https://www.lcsc.com/product-detail/C25907.html","C25907"
"R17,R20,R23","3","1K","","","","Resistor_SMD:R_0402_1005Metric","https://lcsc.com/product-detail/Chip-Resistor-Surface-Mount_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","C106235"
"R16","1","20K","","","","Resistor_SMD:R_0402_1005Metric","https://lcsc.com/product-detail/Chip-Resistor-Surface-Mount_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","C93942"
"R15","1","15K","","","","Resistor_SMD:R_0402_1005Metric","https://lcsc.com/product-detail/Chip-Resistor-Surface-Mount-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","C25756"
"R13","1","2K","","","","Resistor_SMD:R_0402_1005Metric","https://www.lcsc.com/product-detail/C4109.html","C4109"
"R10,R26,R30,R36","4","10K","","","","Resistor_SMD:R_0402_1005Metric","https://lcsc.com/product-detail/Others_Huaxin-S-T-MR04X1002F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","C327797"
"R8","1","5mR 1%/1W","","","","Resistor_SMD:R_1206_3216Metric","https://www.lcsc.com/product-detail/C2988648.html","C2988648"
"R7,R11,R49","3","5.1K","","","","Resistor_SMD:R_0402_1005Metric","https://lcsc.com/product-detail/Chip-Resistor-Surface-Mount_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","C105872"
"R6,R9","2","10R","","","","Resistor_SMD:R_0402_1005Metric","https://www.lcsc.com/product-detail/C25077.html","C25077"
"R5,R12","2","200R","","","","Resistor_SMD:R_0402_1005Metric","https://www.lcsc.com/product-detail/C25087.html","C25087"
"R1,R2,R3,R4,R14,R29,R31,R33,R38,R39,R40,R44,R46,R59,R60","15","100K","","","","Resistor_SMD:R_0402_1005Metric","https://lcsc.com/product-detail/Chip-Resistor-Surface-Mount_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","C60491"
"Q5","1","SI1308EDL","","","","easyeda2kicad-oaf:SOT-323-3_L2.0-W1.3-P1.30-LS2.1-BR","","C7603347"
"Q4","1","SS8050-G","","","","easyeda2kicad-oaf:SOT-23-3_L2.9-W1.3-P1.90-LS2.4-BR","https://lcsc.com/product-detail/Transistors-NPN-PNP_SS8050-L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","C164886"
"Q3","1","CSD83325L","","","","easyeda2kicad-oaf:PICOSTAR-6_L2.2-W1.1-R2-C3-P0.65-BL","","C2860700"
"Q2","1","ZVN4106FTA_C508255","","","","easyeda2kicad-oaf:SOT-23-3_L2.9-W1.3-P1.90-LS2.4-BR","https://lcsc.com/product-detail/MOSFET_Diodes-Incorporated-Z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","C508255"
"Q1","1","SIA445EDJ-T1-GE3","","","","easyeda2kicad-oaf:SC-70-6L_L2.0-W2.0-P0.65-BL","https://lcsc.com/product-detail/MOSFET_VISHAY_SIA445EDJ-T1-G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","C144959"
"NTC1,NTC2","2","NCP15XH103F03RC","","","","easyeda2kicad-oaf:R0402","https://lcsc.com/product-detail/NTC-Thermistors_muRata_NCP15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","C77131"
"LED1,LED2,LED3,LED4","4","TJ-S1608SW6TDSLCCYRGB-A5","","","","easyeda2kicad-oaf:LED-ARRAY-SMD_4P-L1.6-W0.8-BL-FD","","C5356078"
"L3","1","XRIM201210S100MBCA","","","","easyeda2kicad-oaf:L0805","","C39846618"
"L2","1","XGL4020-471MEC","","","","easyeda2kicad-oaf:IND-SMD_L4.0-W4.0_XGL4020","","C5837785"
"L1","1","252012CDMCDDS-1R0MC","","","","easyeda2kicad-oaf:IND-SMD_L2.5-W2.0","https://lcsc.com/product-detail/New-Arrivals_Sumida-252012CD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","C492725"
"FPC1","1","FPC 0.5-24P LTH2.0","","","","easyeda2kicad-oaf:FPC-SMD_FPC-0.5-24P-LTH2.0","","C6081230"
"F1","1","BSMD1206-075-6V","","","","easyeda2kicad-oaf:F1206","https://lcsc.com/product-detail/PTC-Resettable-Fuses_BHFUSE-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","C883127"
"D3,D4,D5","3","PMEG3005EL,315","","","","easyeda2kicad-oaf:SOD-882_L1.0-W0.6-RD","https://lcsc.com/product-detail/Schottky-Barrier-Diodes-SBD_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","C282565"
"CN1,CN2,CN3","3","HCZZ0032-5","","","","easyeda2kicad-oaf:CONN-SMD_HCZZ0032-5","","C7433426"
"C71","1","0.1uF/25V","DNP","","","Capacitor_SMD:C_0402_1005Metric","https://lcsc.com/product-detail/Multilayer-Ceramic-Capacitor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","C100072"
"C69","1","0.1uF/16V","","","","Capacitor_SMD:C_0402_1005Metric","https://lcsc.com/product-detail/Multilayer-Ceramic-Capacitor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","C1525"
"C42","1","1uF/50V","DNP","","","Capacitor_SMD:C_0402_1005Metric","https://lcsc.com/product-detail/Multilayer-Ceramic-Capacitor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","C7500380"
"C33","1","500pF/50V","","","","Capacitor_SMD:C_0603_1608Metric","https://lcsc.com/product-detail/Multilayer-Ceramic-Capacitor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","C1624"
"C27","1","0.47uF/25V","","","","Capacitor_SMD:C_0402_1005Metric","https://www.lcsc.com/product-detail/C2934765.html","C2934765"
"C21","1","22uF/10V","","","","Capacitor_SMD:C_0402_1005Metric","https://www.lcsc.com/product-detail/C6119813.html","C6119813"
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
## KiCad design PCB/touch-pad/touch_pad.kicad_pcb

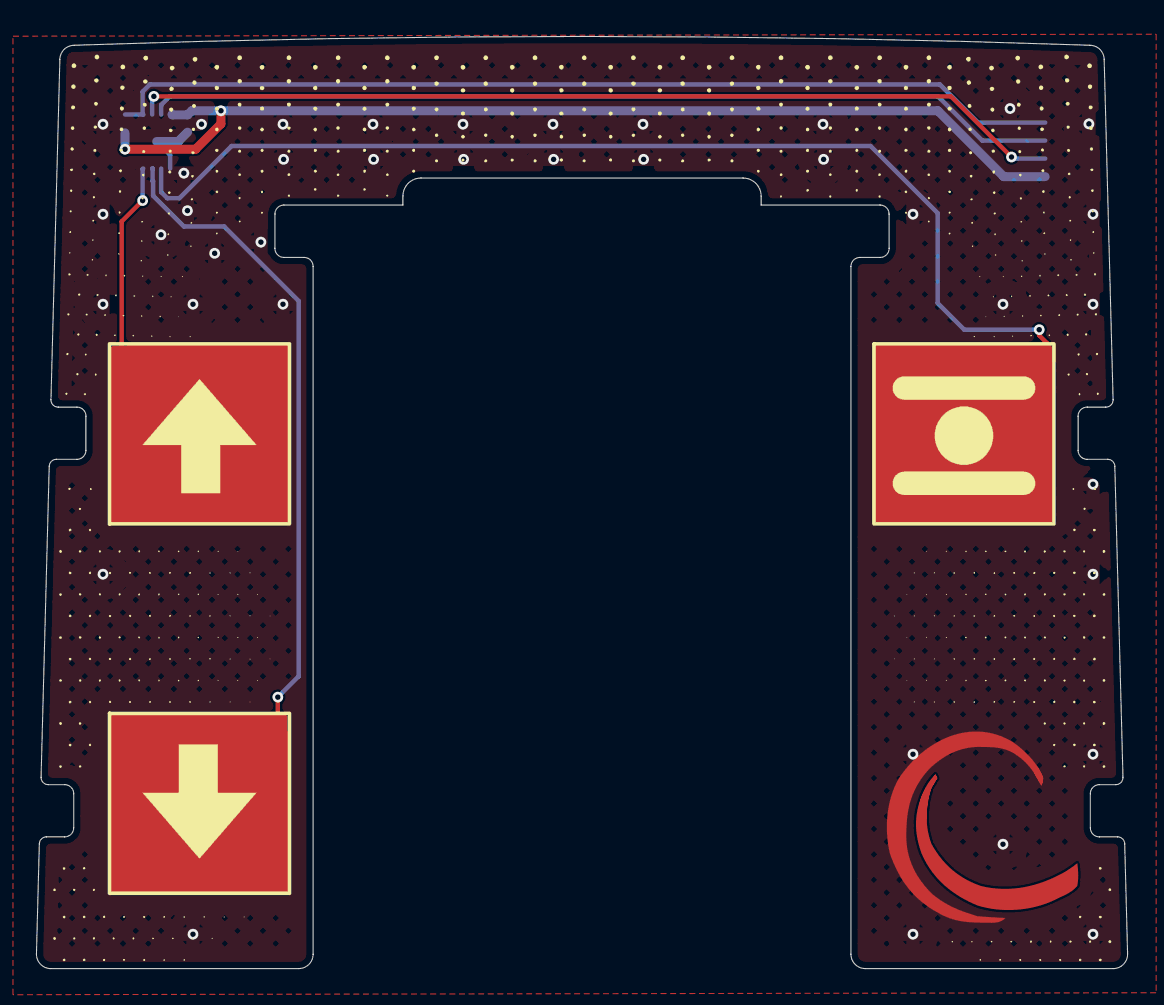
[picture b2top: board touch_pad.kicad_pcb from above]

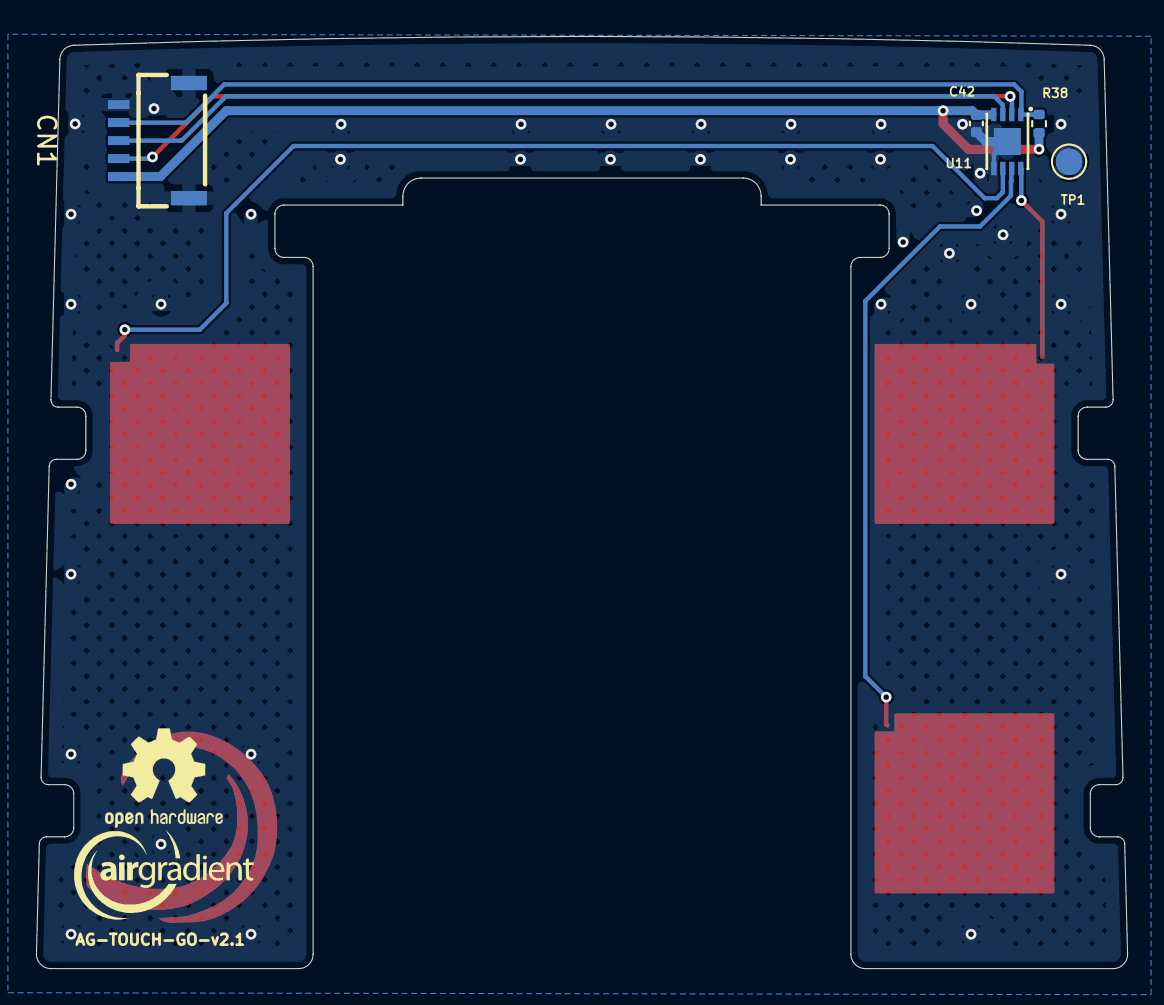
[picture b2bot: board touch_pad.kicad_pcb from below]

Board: 2 copper layers, 60.6 x 51.8 mm, 8 parts (5 on the bottom side), 8 nets.

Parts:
C42: 0.1uF/25V; C_0402_1005Metric
CN1: HCZZ0032-5; CONN-SMD_HCZZ0032-5
R38: 100K; R_0402_1005Metric
T1, T2, T3: tourch_pad
TP1: TestPoint; TestPoint_Pad_D1.5mm
U11: CAP1203-1-AC3-TR; TDFN-8_L3.0-W2.0-P0.50-BL-EP

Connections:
/INT: CN1.4, R38.1, U11.1 (~ALERT)
/SCL: CN1.3, U11.3 (SMCLK)
/SDA: CN1.2, U11.2 (SMDATA)
GND: C42.1, CN1.5, CN1.6, CN1.7, TP1.1 (1_1), U11.5 (GND), U11.9 (EP)
unnamed: T1.1 (1_1), U11.8 (CS1)
unnamed: T2.1 (1_1), U11.7 (CS2)
unnamed: T3.1 (1_1), U11.6 (CS3)
VCC: C42.2, CN1.1, R38.2, U11.4 (VDD)

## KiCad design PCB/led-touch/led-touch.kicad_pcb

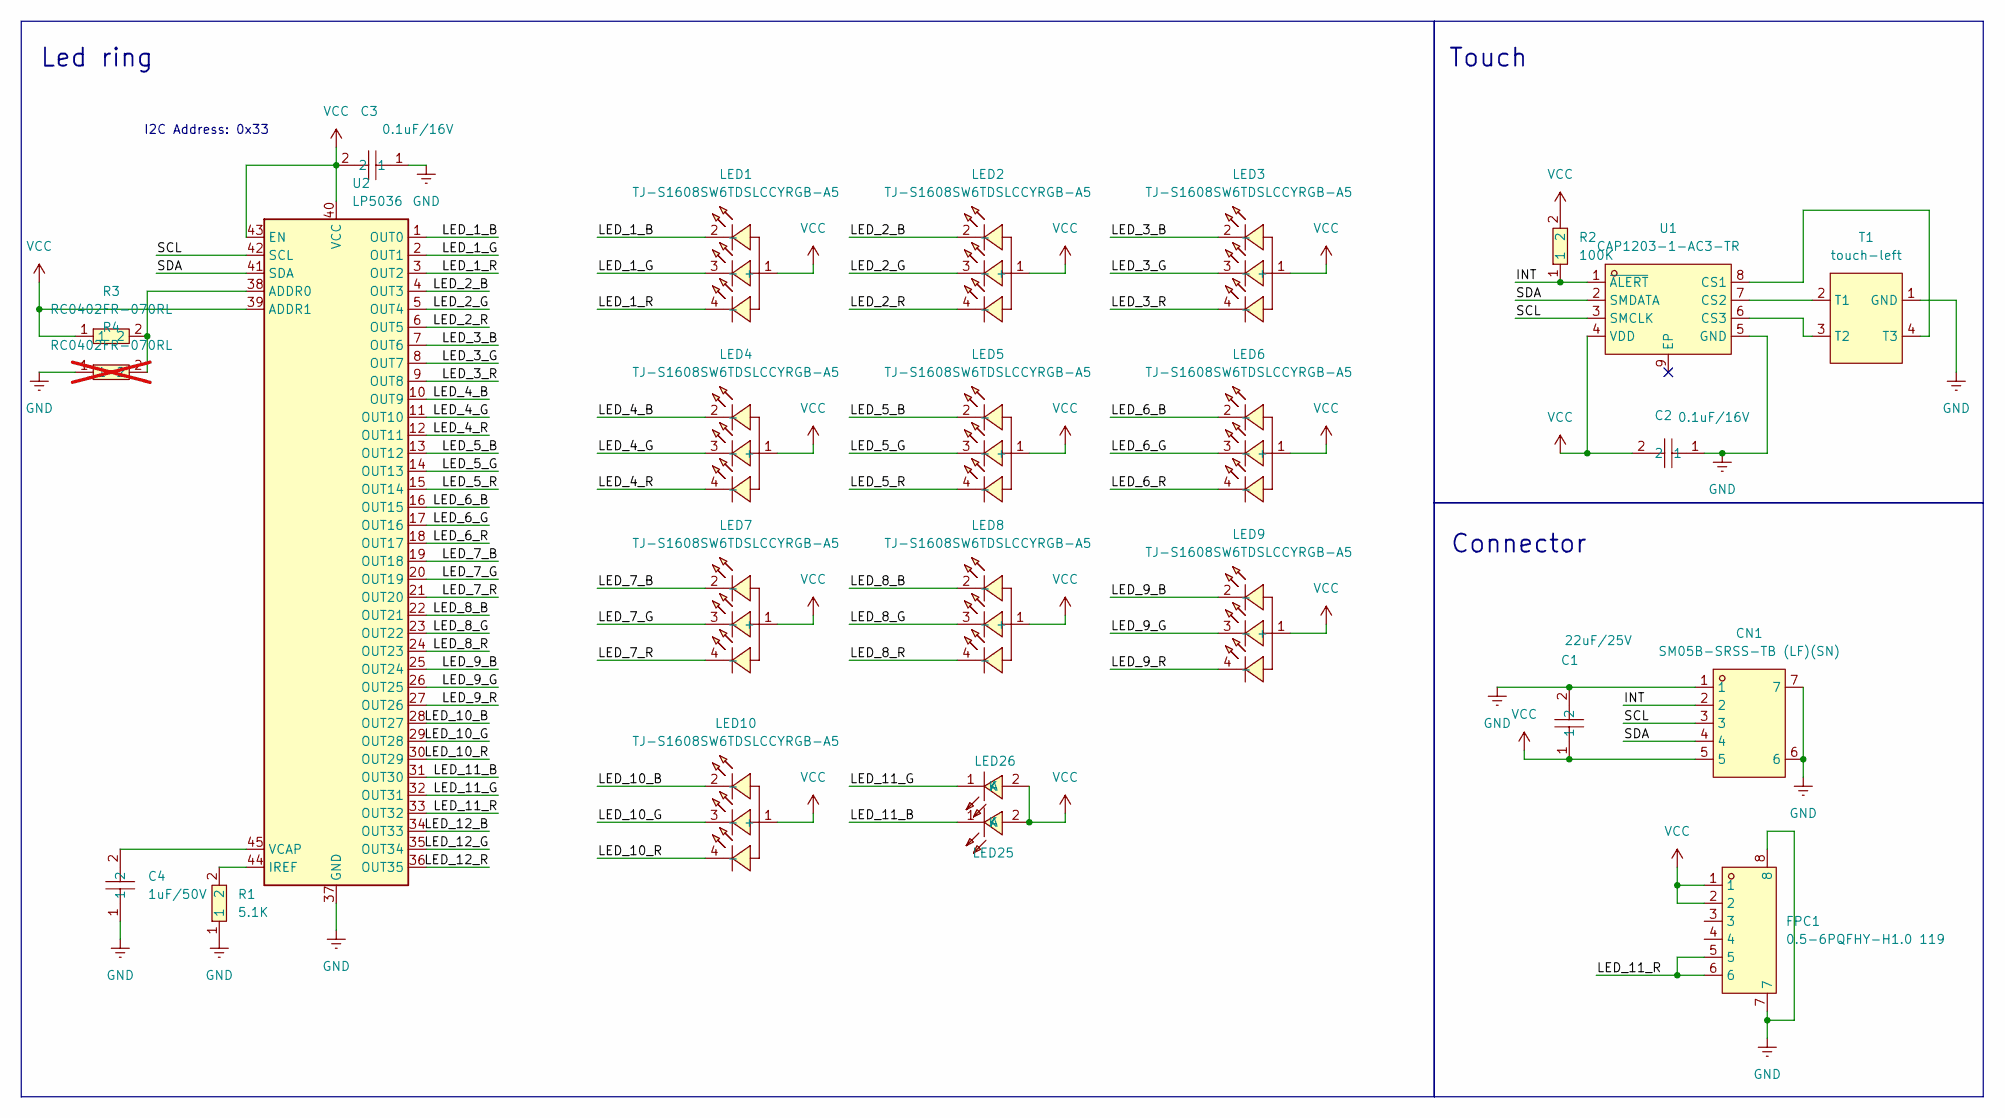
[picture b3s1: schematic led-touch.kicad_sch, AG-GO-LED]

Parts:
C1: 22uF/25V; C_0805_2012Metric; LCSC Part C602037
C2, C3: 0.1uF/16V; C_0402_1005Metric; LCSC Part C1525
C4: 1uF/50V; C_0402_1005Metric; LCSC Part C7500380
CN1: SM05B-SRSS-TB (LF)(SN); CONN-SMD_SM05B-SRSS-TB-LF-SN; LCSC Part C136657
FPC1: 0.5-6PQFHY-H1.0 119; FPC-SMD_6P-P0.50_0.5-6PQFHY-H1.0119; LCSC Part C2858296
LED1, LED2, LED3, LED4, LED5, LED6, LED7, LED8, LED9, LED10: TJ-S1608SW6TDSLCCYRGB-A5; LED-ARRAY-SMD_4P-L1.6-W0.8-BL-FD; LCSC Part C5356078
LED25, LED26: 99-213UMC/3640661/TR8-T; LED-SMD_L2.8-W1.2-RD; LCSC Part C181869
R1: 5.1K; R_0402_1005Metric; LCSC Part C105872
R2: 100K; R_0402_1005Metric; LCSC Part C60491
R3: RC0402FR-070RL; R_0402_1005Metric; LCSC Part C106231
R4: RC0402FR-070RL; R_0402_1005Metric; LCSC Part C106231; not fitted
T1: touch-left; touch-pad-go
U1: CAP1203-1-AC3-TR; TDFN-8_L3.0-W2.0-P0.50-BL-EP; LCSC Part C2652075
U2: LP5036; VQFN-46-1EP_5x6mm_P0.4mm_EP2.8x3.8mm

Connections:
/INT: CN1.2, R2.1, U1.1 (~ALERT)
/LED_1_B: LED1.2 (-), U2.1 (OUT0)
/LED_1_G: LED1.3 (-), U2.2 (OUT1)
/LED_1_R: LED1.4 (-), U2.3 (OUT2)
/LED_2_B: LED2.2 (-), U2.4 (OUT3)
/LED_2_G: LED2.3 (-), U2.5 (OUT4)
/LED_2_R: LED2.4 (-), U2.6 (OUT5)
/LED_3_B: LED3.2 (-), U2.7 (OUT6)
/LED_3_G: LED3.3 (-), U2.8 (OUT7)
/LED_3_R: LED3.4 (-), U2.9 (OUT8)
/LED_4_B: LED4.2 (-), U2.10 (OUT9)
/LED_4_G: LED4.3 (-), U2.11 (OUT10)
/LED_4_R: LED4.4 (-), U2.12 (OUT11)
/LED_5_B: LED5.2 (-), U2.13 (OUT12)
/LED_5_G: LED5.3 (-), U2.14 (OUT13)
/LED_5_R: LED5.4 (-), U2.15 (OUT14)
/LED_6_B: LED6.2 (-), U2.16 (OUT15)
/LED_6_G: LED6.3 (-), U2.17 (OUT16)
/LED_6_R: LED6.4 (-), U2.18 (OUT17)
/LED_7_B: LED7.2 (-), U2.19 (OUT18)
/LED_7_G: LED7.3 (-), U2.20 (OUT19)
/LED_7_R: LED7.4 (-), U2.21 (OUT20)
/LED_8_B: LED8.2 (-), U2.22 (OUT21)
/LED_8_G: LED8.3 (-), U2.23 (OUT22)
/LED_8_R: LED8.4 (-), U2.24 (OUT23)
/LED_9_B: LED9.2 (-), U2.25 (OUT24)
/LED_9_G: LED9.3 (-), U2.26 (OUT25)
/LED_9_R: LED9.4 (-), U2.27 (OUT26)
/LED_10_B: LED10.2 (-), U2.28 (OUT27)
/LED_10_G: LED10.3 (-), U2.29 (OUT28)
/LED_10_R: LED10.4 (-), U2.30 (OUT29)
/LED_11_B: LED25.1 (K), U2.31 (OUT30)
/LED_11_G: LED26.1 (K), U2.32 (OUT31)
/LED_11_R: FPC1.5, FPC1.6, U2.33 (OUT32)
/LED_12_B: U2.34 (OUT33)
/LED_12_G: U2.35 (OUT34)
/LED_12_R: U2.36 (OUT35)
/SCL: CN1.3, U1.3 (SMCLK), U2.42 (SCL)
/SDA: CN1.4, U1.2 (SMDATA), U2.41 (SDA)
GND: C1.2, C2.1, C3.1, C4.1, CN1.1, CN1.6, CN1.7, FPC1.7, FPC1.8, R1.1, R4.1, T1.1 (GND), U1.5 (GND), U2.37 (GND), U2.46 (GND), U2.47 (GND)
unnamed: T1.2 (T1), U1.7 (CS2)
unnamed: T1.3 (T2), U1.6 (CS3)
unnamed: T1.4 (T3), U1.8 (CS1)
unnamed: R3.2, R4.2, U2.38 (ADDR0)
unnamed: R1.2, U2.44 (IREF)
unnamed: C4.2, U2.45 (VCAP)
VCC: C1.1, C2.2, C3.2, CN1.5, FPC1.1, FPC1.2, LED1.1 (+), LED2.1 (+), LED3.1 (+), LED4.1 (+), LED5.1 (+), LED6.1 (+), LED7.1 (+), LED8.1 (+), LED9.1 (+), LED10.1 (+), LED25.2 (A), LED26.2 (A), R2.2, R3.1, U1.4 (VDD), U2.39 (ADDR1), U2.40 (VCC), U2.43 (EN)

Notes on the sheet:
I2C Address: 0x33
Touch
Connector
Led ring
